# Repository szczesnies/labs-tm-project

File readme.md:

# Projekt z Techniki Mikroprocesorowej

Wykorzystanie minrokontrolera Atmega328 do odczytu temperatury i wilgoci otoczenia

# Założenie projektu
Odczyt temperatury i wilgoci przy użyciu mikrokontrolera AVR ATmega328 

# Do skonstruowania projektu zostały użyte elementy:
- Arduino Uno z mikrokontrolerem Atmega 328
- sensor DHT 11
- wyświetlacz znakowy 2x16 z konwerterem I2C
- przewody połączeniowe

#

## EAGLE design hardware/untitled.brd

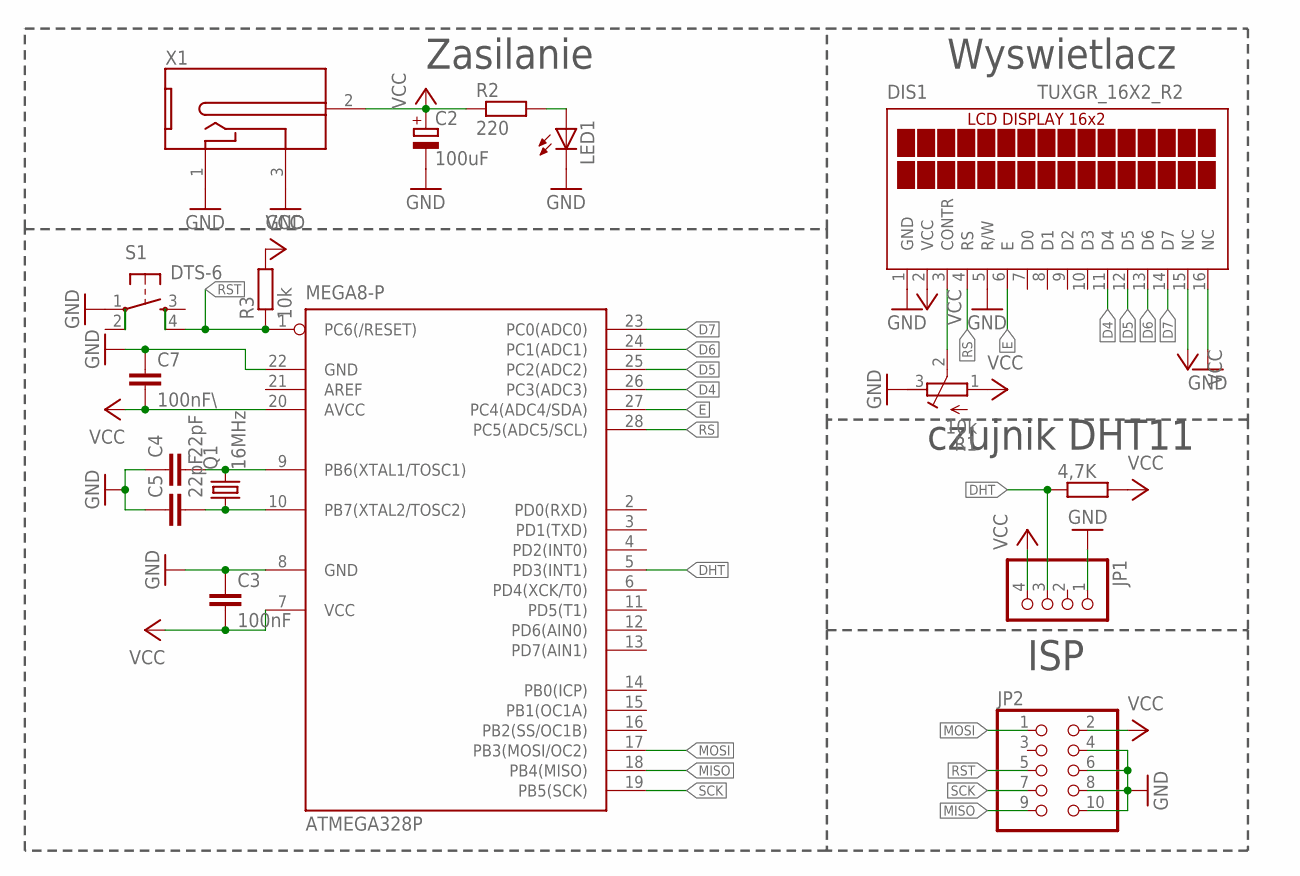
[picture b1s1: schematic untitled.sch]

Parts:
4,7K: R-EU_0204/7; 0204/7
ATMEGA328P: MEGA8-P; DIL28-3
C2: 100uF; E2,5-6
C3: 100nF; C025-025X050
C4, C5: 22pF; C025-025X050
C7: 100nF\; C025-025X050
DIS1: TUXGR_16X2_R2
JP1: PINHD-1X4; 1X04
JP2: PINHD-2X5; 2X05
LED1: LED3MM
Q1: 16MHz; HC49/S
R1: 10k; RTRIM3339P
R2: 220; 0204/7
R3: 10k; 0204/7
S1: DTS-6
X1: DC-2.1MM-5MM; DC-21MM

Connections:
D4: ATMEGA328P.26 (PC3(ADC3)), DIS1.11 (D4)
D5: ATMEGA328P.25 (PC2(ADC2)), DIS1.12 (D5)
D6: ATMEGA328P.24 (PC1(ADC1)), DIS1.13 (D6)
D7: ATMEGA328P.23 (PC0(ADC0)), DIS1.14 (D7)
DHT: 4,7K.1, ATMEGA328P.5 (PD3(INT1)), JP1.3
E: ATMEGA328P.27 (PC4(ADC4/SDA)), DIS1.6 (E)
GND: ATMEGA328P.8 (GND), ATMEGA328P.22 (GND), C2.-, C3.1, C4.1, C5.1, C7.1, DIS1.1 (GND), DIS1.5 (R/W), DIS1.16 (NC), JP1.1, JP2.4, JP2.6, JP2.8, JP2.10, LED1.K (C), R1.3 (A), S1.1, X1.1, X1.3 (2)
MISO: ATMEGA328P.18 (PB4(MISO)), JP2.9
MOSI: ATMEGA328P.17 (PB3(MOSI/OC2)), JP2.1
unnamed: LED1.A, R2.2
unnamed: ATMEGA328P.10 (PB7(XTAL2/TOSC2)), C5.2, Q1.1
unnamed: ATMEGA328P.9 (PB6(XTAL1/TOSC1)), C4.2, Q1.2
unnamed: DIS1.3 (CONTR), R1.2 (S)
RS: ATMEGA328P.28 (PC5(ADC5/SCL)), DIS1.4 (RS)
RST: ATMEGA328P.1 (PC6(/RESET)), JP2.5, R3.1, S1.4
SCK: ATMEGA328P.19 (PB5(SCK)), JP2.7
VCC: 4,7K.2, ATMEGA328P.7 (VCC), ATMEGA328P.20 (AVCC), C2.+, C3.2, C7.2, DIS1.2 (VCC), DIS1.15 (NC), JP1.4, JP2.2, R1.1 (E), R2.1, R3.2, X1.2 (3)

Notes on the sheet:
Wyswietlacz
czujnik DHT11
ISP
Zasilanie

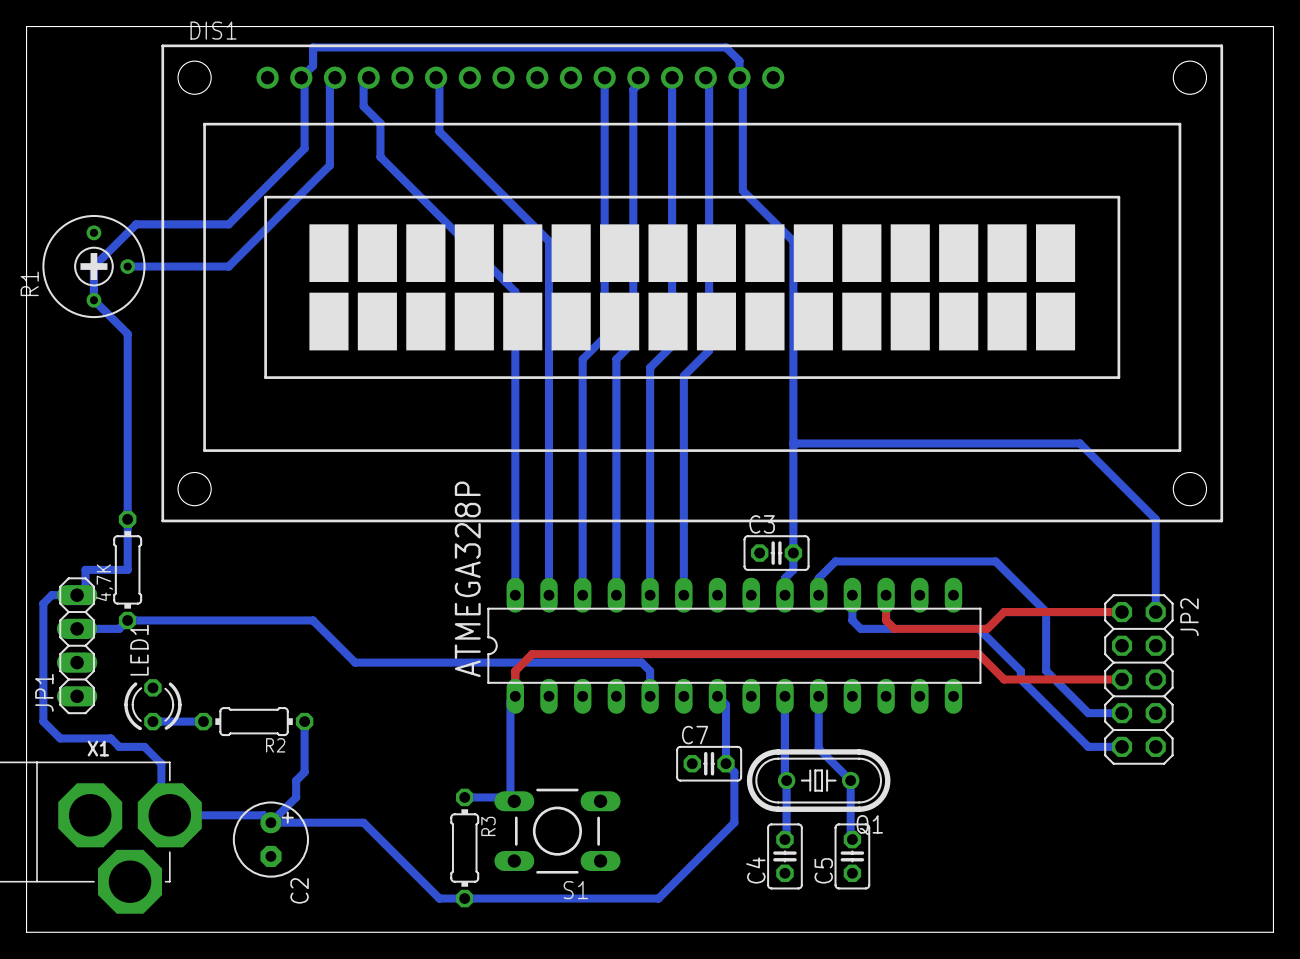
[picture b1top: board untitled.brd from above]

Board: 2 copper layers, 94.0 x 68.2 mm, 17 parts (0 on the bottom side), 17 nets.

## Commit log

2021-11-08 init
